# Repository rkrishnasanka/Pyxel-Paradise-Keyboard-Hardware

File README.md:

# Pyxel-Paradise

## Keymap

| Button              	| Arduino 	|
|---------------------	|---------	|
| North               	| 2       	|
| East                	| 5       	|
| South               	| 3       	|
| West                	| 4       	|
| Meta-Button-1       	| 15      	|
| Meta-Button-2       	| 14      	|
| Meta-Button-3       	| 16      	|
| Meta-Button-4       	| 10      	|
| ARCADE-BUTTON-UP    	| 6       	|
| ARCADE-BUTTON-LEFT  	| 7       	|
| ARCADE-BUTTON-RIGHT 	| 8       	|
| ARCADE-BUTTON-DOWN  	| 9       	|

## License

<br />This work is licensed under a <a rel="license" href="http://creativecommons.org/licenses/by-nc-sa/4.0/">Creative Commons Attribution-NonCommercial-ShareAlike 4.0 International License</a>.

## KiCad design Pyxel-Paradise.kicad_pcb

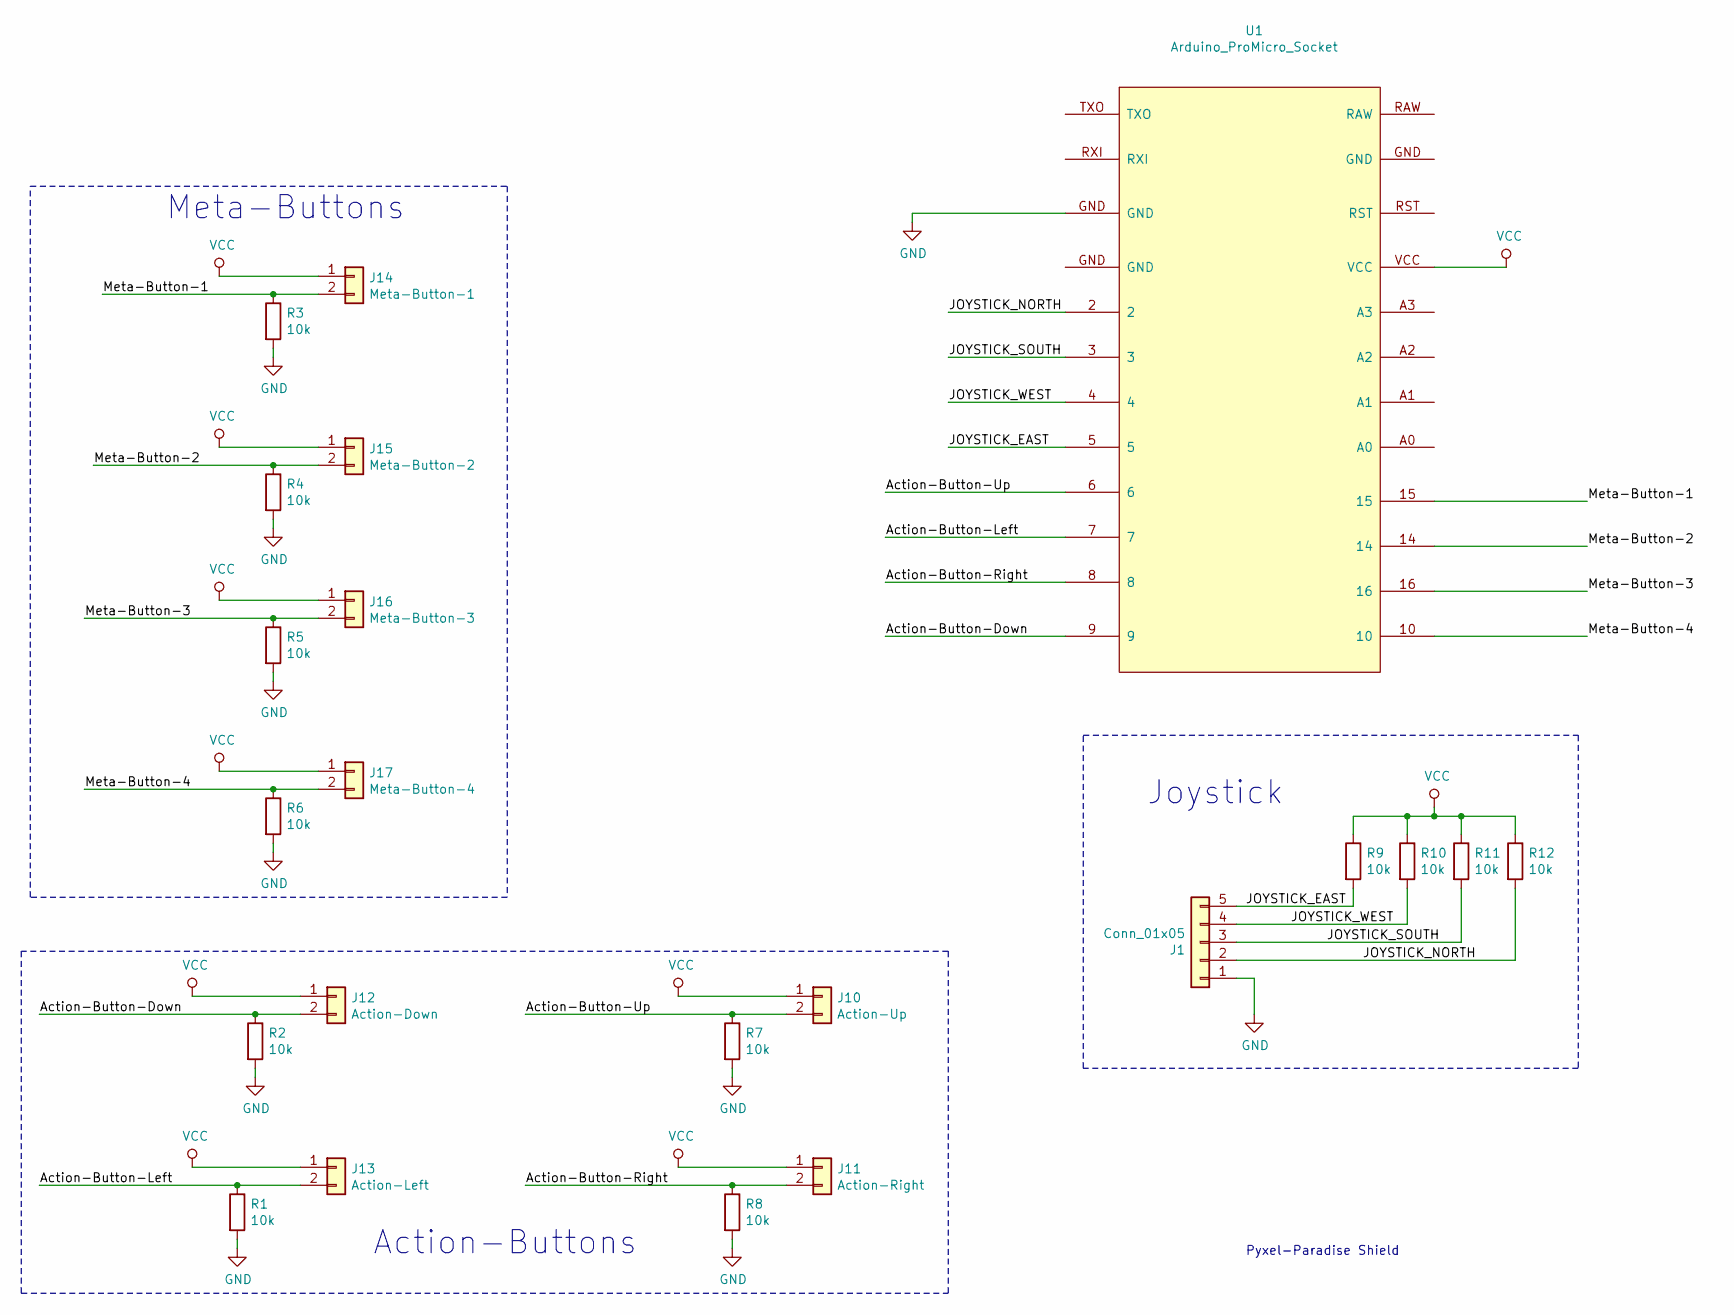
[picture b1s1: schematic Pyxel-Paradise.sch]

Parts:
J1: Conn_01x05; JST_XH_B05B-XH-A_1x05_P2.50mm_Vertical
J10: Action-Up; JST_XH_B02B-XH-A_1x02_P2.50mm_Vertical
J11: Action-Right; JST_XH_B02B-XH-A_1x02_P2.50mm_Vertical
J12: Action-Down; JST_XH_B02B-XH-A_1x02_P2.50mm_Vertical
J13: Action-Left; JST_XH_B02B-XH-A_1x02_P2.50mm_Vertical
J14: Meta-Button-1; JST_XH_B02B-XH-A_1x02_P2.50mm_Vertical
J15: Meta-Button-2; JST_XH_B02B-XH-A_1x02_P2.50mm_Vertical
J16: Meta-Button-3; JST_XH_B02B-XH-A_1x02_P2.50mm_Vertical
J17: Meta-Button-4; JST_XH_B02B-XH-A_1x02_P2.50mm_Vertical
R1, R2, R3, R4, R5, R6, R7, R8, R9, R10, R11, R12: 10k; R_Axial_DIN0207_L6.3mm_D2.5mm_P2.54mm_Vertical
U1: Arduino_ProMicro_Socket; Aruduino_ProMicro_Socket

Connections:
/Action-Button-Down: J12.2, R2.1, U1.9
/Action-Button-Left: J13.2, R1.1, U1.7
/Action-Button-Right: J11.2, R8.1, U1.8
/Action-Button-Up: J10.2, R7.1, U1.6
/JOYSTICK_EAST: J1.5, R9.2, U1.5
/JOYSTICK_NORTH: J1.2, R12.2, U1.2
/JOYSTICK_SOUTH: J1.3, R11.2, U1.3
/JOYSTICK_WEST: J1.4, R10.2, U1.4
/Meta-Button-1: J14.2, R3.1, U1.15
/Meta-Button-2: J15.2, R4.1, U1.14
/Meta-Button-3: J16.2, R5.1, U1.16
/Meta-Button-4: J17.2, R6.1, U1.10
GND: J1.1, R1.2, R2.2, R3.2, R4.2, R5.2, R6.2, R7.2, R8.2, U1.GND
VCC: J10.1, J11.1, J12.1, J13.1, J14.1, J15.1, J16.1, J17.1, R9.1, R10.1, R11.1, R12.1, U1.VCC

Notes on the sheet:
Joystick
Meta-Buttons
Action-Buttons
Pyxel-Paradise Shield

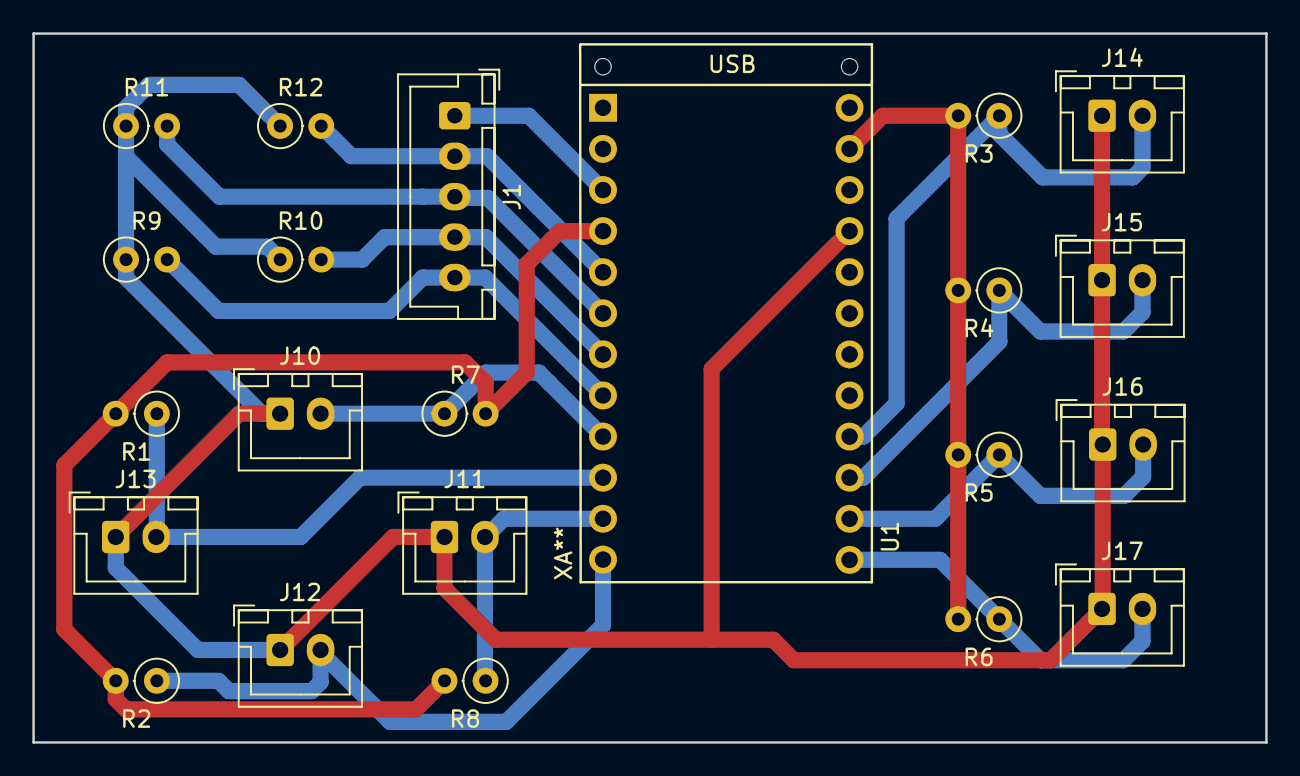
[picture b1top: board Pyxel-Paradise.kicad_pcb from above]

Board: 2 copper layers, 76.2 x 43.8 mm, 22 parts (0 on the bottom side), 14 nets.

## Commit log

2018-09-23 Finished the first version of the Pyxel-Paradise board with GPIO inputs
2018-09-23 Added readme and lisence
2019-08-27 V1 of a working PCB is complete
